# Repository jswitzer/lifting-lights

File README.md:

Lifting lights: An arduino / XBEE project to enable three weightlifting judges to signal white (good) or red (bad) during a powerlifting competition.

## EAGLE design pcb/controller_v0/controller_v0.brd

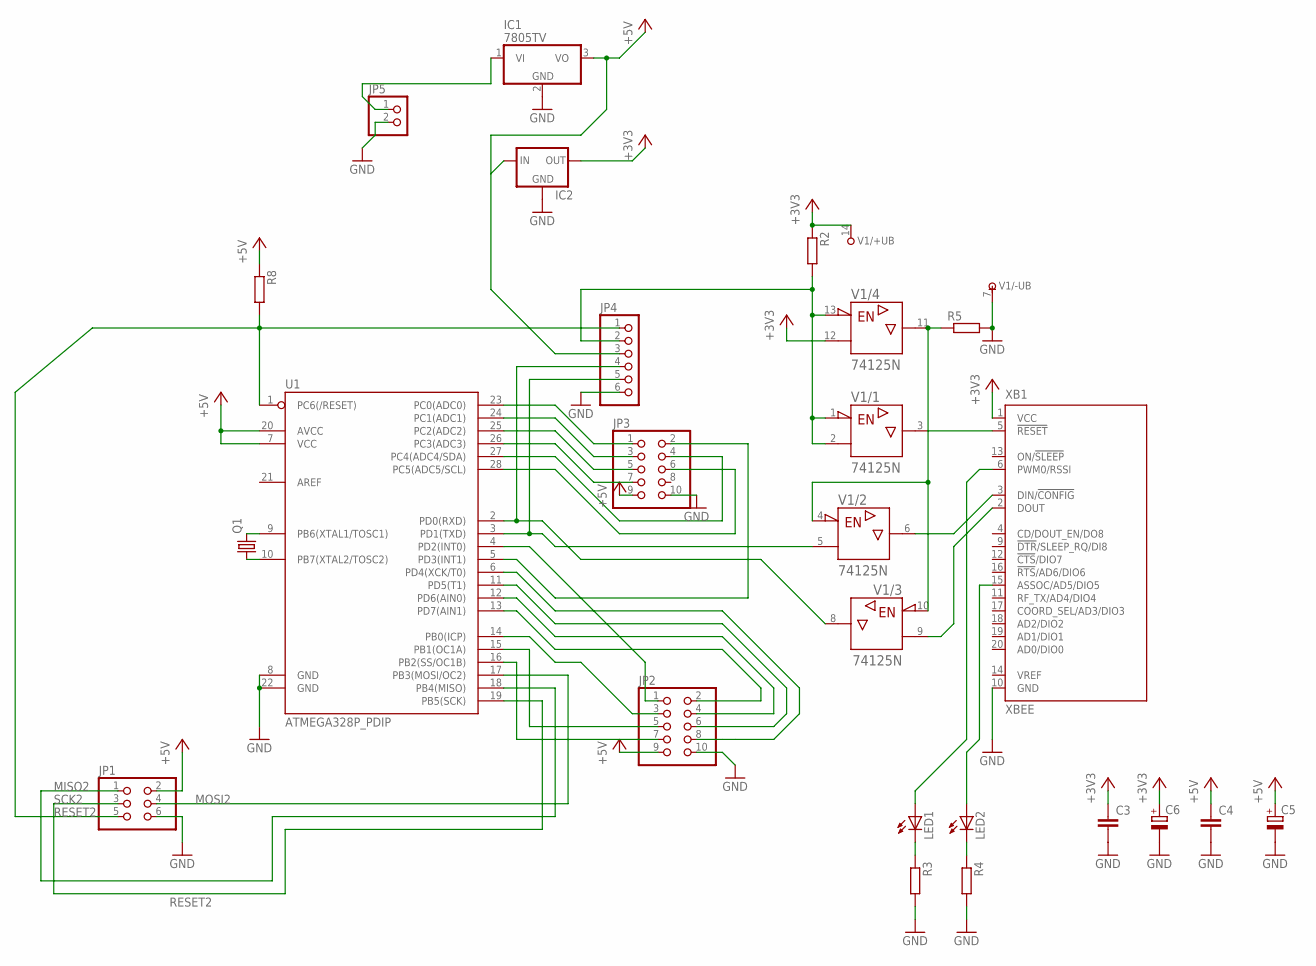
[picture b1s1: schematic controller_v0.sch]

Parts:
C3, C4: C-EU025-025X050; C025-025X050
C5, C6: CPOL-EUE2.5-6; E2,5-6
IC1: 7805TV; TO220V
IC2: 78LXX
JP1: PINHD-2X3; 2X03
JP2, JP3: PINHD-2X5; 2X05
JP4: PINHD-1X6; 1X06
JP5: PINHD-1X2; 1X02
LED1, LED2: LED3MM
Q1: CRYSTALHC49S; HC49/S
R2, R3, R4, R5, R8: R-EU_0204/7; 0204/7
U1: ATMEGA328P_PDIP; DIL28-3
V1: 74125N; DIL14
XB1: XBEE

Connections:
+3V3: C3.1, C6.+, IC2.OUT, R2.1, V1.12 (A), V1.14 (+UB), XB1.1 (VCC)
+5V: C4.1, C5.+, IC1.3 (VO), IC2.IN, JP1.2, JP2.9, JP3.9, JP4.3, R8.1, U1.7 (VCC), U1.20 (AVCC)
GND: C3.2, C4.2, C5.-, C6.-, IC1.2 (GND), IC2.GND, JP1.6, JP2.10, JP3.10, JP4.6, JP5.2, R3.2, R4.2, R5.2, U1.8 (GND), U1.22 (GND), V1.7 (-UB), XB1.10 (GND)
MISO2: JP1.1, U1.18 (PB4(MISO))
MOSI2: JP1.4, U1.17 (PB3(MOSI/OC2))
unnamed: Q1.2, U1.9 (PB6(XTAL1/TOSC1))
unnamed: Q1.1, U1.10 (PB7(XTAL2/TOSC2))
unnamed: V1.6 (Y), XB1.3 (DIN/!CONFIG)
unnamed: V1.3 (Y), XB1.5 (!RESET)
unnamed: LED2.A, XB1.15 (ASSOC/AD5/DIO5)
unnamed: JP4.5, U1.3 (PD1(TXD)), V1.5 (A)
unnamed: LED1.K (C), R3.1
unnamed: LED2.K (C), R4.1
unnamed: LED1.A, XB1.6 (PWM0/RSSI)
unnamed: JP4.4, U1.2 (PD0(RXD)), V1.8 (Y)
unnamed: V1.9 (A), XB1.2 (DOUT)
unnamed: R5.1, V1.4 (!G), V1.10 (!G), V1.11 (Y)
unnamed: JP2.7, U1.16 (PB2(SS/OC1B))
unnamed: JP4.2, R2.2, V1.1 (!G), V1.2 (A), V1.13 (!G)
unnamed: JP2.5, U1.15 (PB1(OC1A))
unnamed: JP2.1, U1.4 (PD2(INT0))
unnamed: JP2.4, U1.12 (PD6(AIN0))
unnamed: JP3.1, U1.23 (PC0(ADC0))
unnamed: JP3.3, U1.24 (PC1(ADC1))
unnamed: JP2.8, U1.6 (PD4(XCK/T0))
unnamed: JP3.2, U1.5 (PD3(INT1))
unnamed: JP3.5, U1.25 (PC2(ADC2))
unnamed: JP3.7, U1.26 (PC3(ADC3))
unnamed: JP3.4, U1.27 (PC4(ADC4/SDA))
unnamed: JP3.6, U1.28 (PC5(ADC5/SCL))
unnamed: JP2.6, U1.11 (PD5(T1))
unnamed: JP2.2, U1.13 (PD7(AIN1))
unnamed: JP2.3, U1.14 (PB0(ICP))
unnamed: IC1.1 (VI), JP5.1
RESET2: JP1.5, JP4.1, R8.2, U1.1 (PC6(/RESET))
SCK2: JP1.3, U1.19 (PB5(SCK))

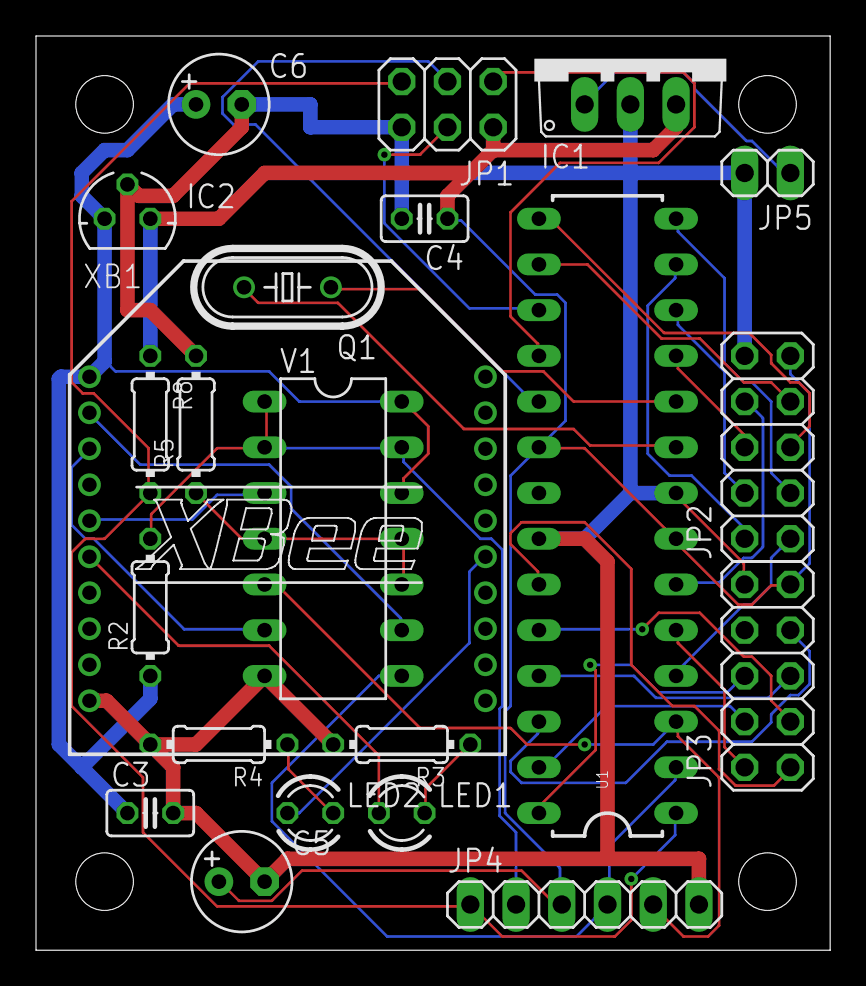
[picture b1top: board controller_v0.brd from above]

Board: 2 copper layers, 44.1 x 50.8 mm, 22 parts (0 on the bottom side), 36 nets.

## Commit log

2021-06-23 Publish code from private repo

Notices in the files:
parts and their libraries:
SparkFun-DigitalIC: Licensing: Creative Commons ShareAlike 4.0 International - https://creativecommons.org/licenses/by-sa/4.0
